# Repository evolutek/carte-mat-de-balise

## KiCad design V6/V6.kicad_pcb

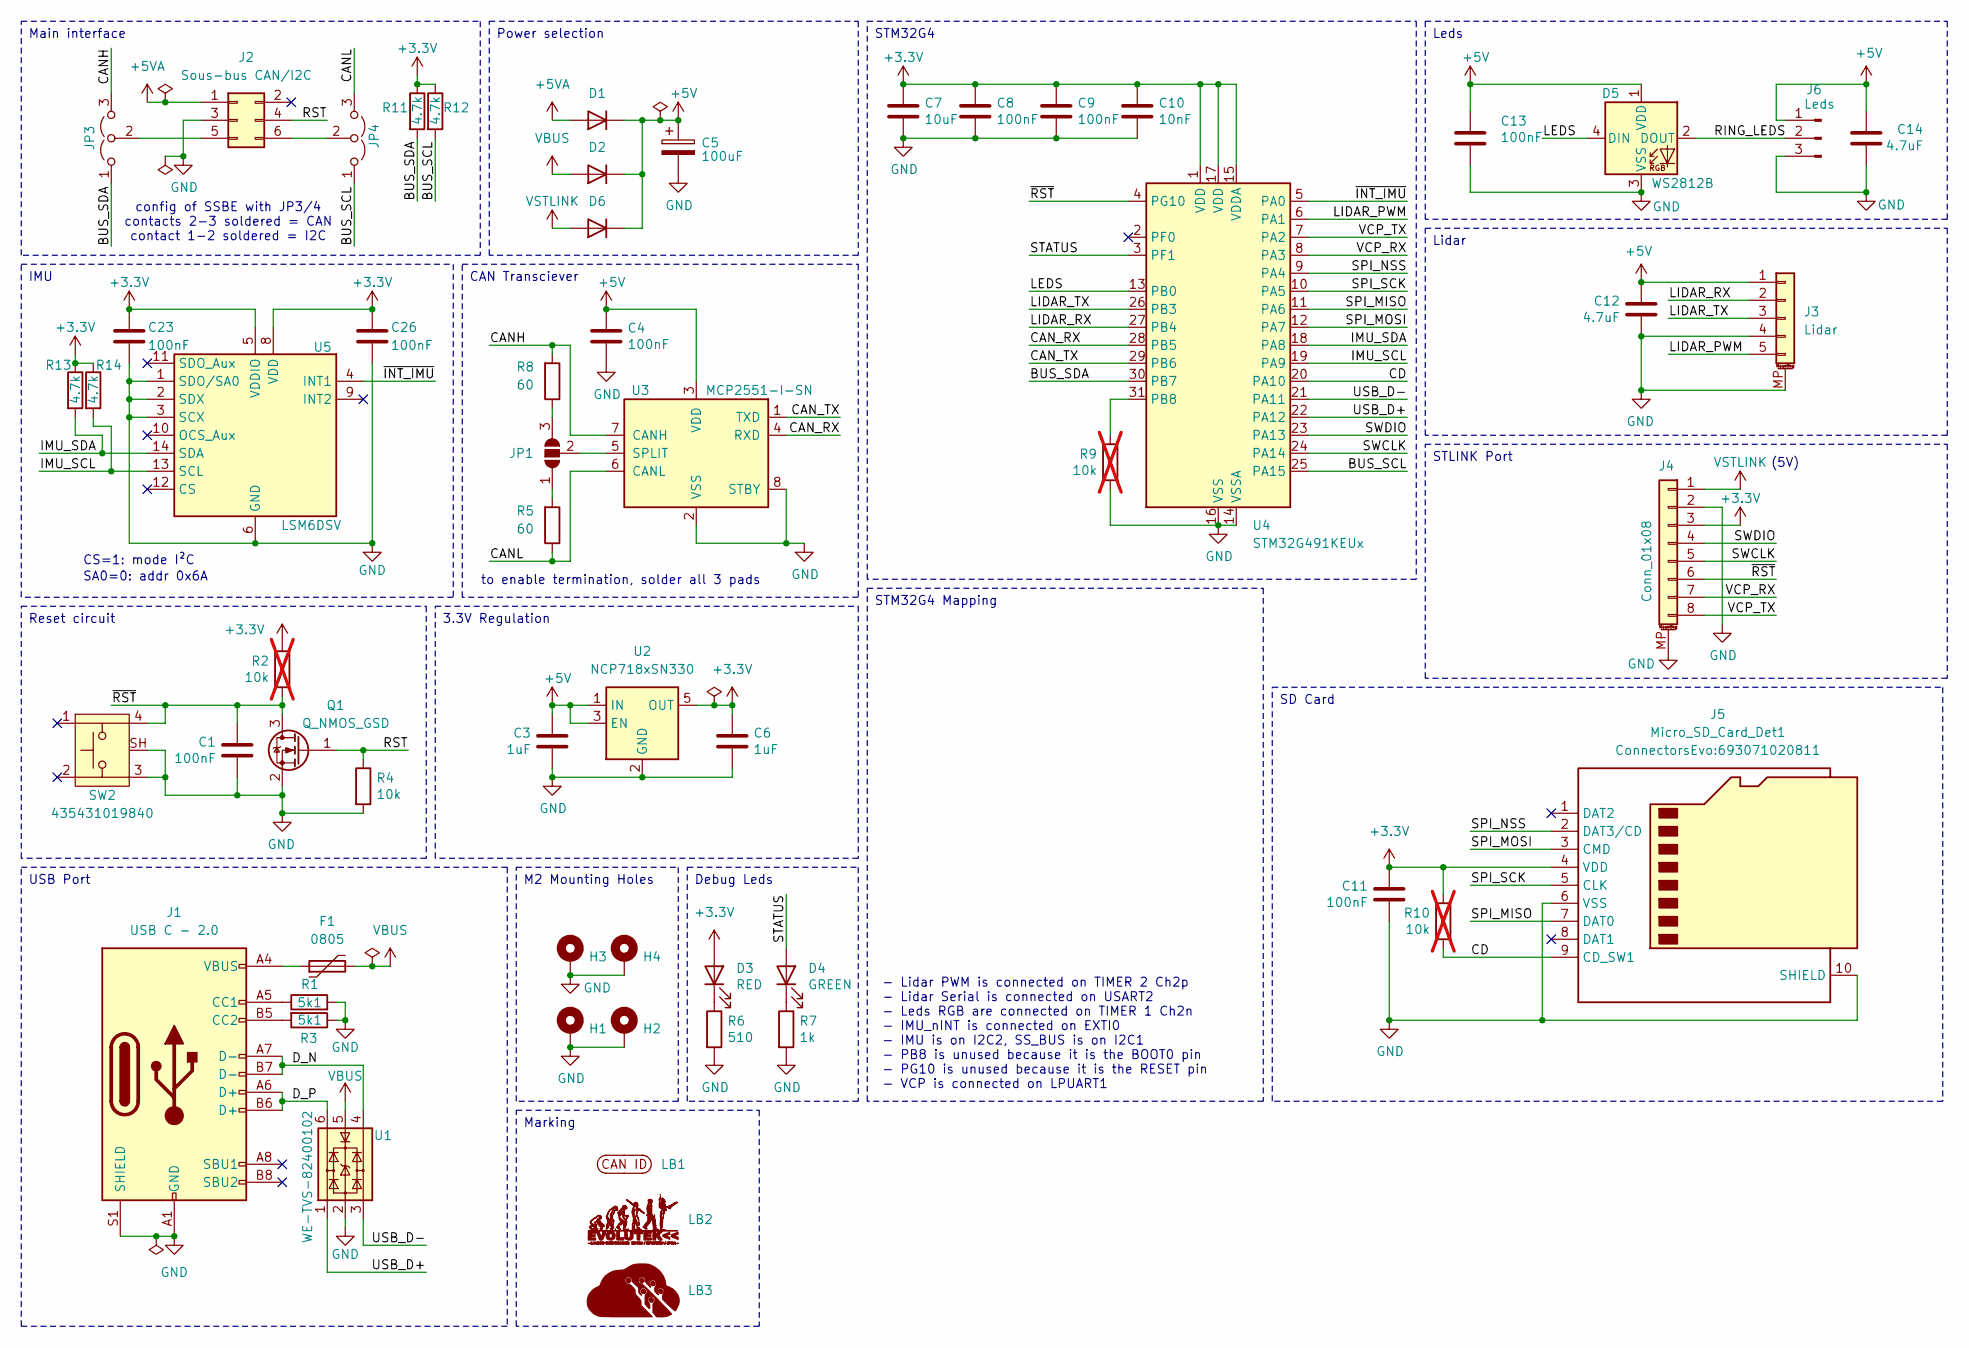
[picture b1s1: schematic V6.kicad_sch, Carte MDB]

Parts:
C1, C4, C8, C9, C11, C13, C23, C26: 100nF; C_0603_1608Metric
C3, C6: 1uF; C_0603_1608Metric
C5: 100uF; C_Elec_6.3x7.7
C7: 10uF; C_0603_1608Metric
C10: 10nF; C_0603_1608Metric
C12, C14: 4.7uF; C_0603_1608Metric
D1, D2, D6: D; D_SOD-523
D3: RED; LED_0805_2012Metric
D4: GREEN; LED_0805_2012Metric
D5: WS2812B; LED_WS2812B_PLCC4_5.0x5.0mm_P3.2mm
F1: 0805; C_0805_2012Metric
H1, H2, H3, H4: MountingHole_Pad; MountingHole_2.2mm_M2_Pad_Via
J1: USB C - 2.0; USB_C_Receptacle_GCT_USB4105-xx-A_16P_TopMnt_Horizontal
J2: Sous-bus CAN/I2C; 690367280676
J3: Lidar; 648105131822
J4: Conn_01x08; 686108188622
J5: Micro_SD_Card_Det1; 693071020811
J6: Leds; S03B-PASK
JP1: Jumper_3_Open; SolderJumper-3_P1.3mm_Open_RoundedPad1.0x1.5mm
JP3, JP4: Jumper_3_Open; SolderJumper-3_P1.3mm_Open_RoundedPad1.0x1.5mm_NumberLabels
LB1: CAN ID lablel
LB2: LOGO; logo-evo-min
LB3: LOGO; Logo Aisler Min
Q1: Q_NMOS_GSD; SOT-23
R1, R3: 5k1; R_0603_1608Metric
R2, R9, R10: 10k; R_0603_1608Metric; not fitted
R4: 10k; R_0603_1608Metric
R5, R8: 60; R_0603_1608Metric
R6: 510; R_0603_1608Metric
R7: 1k; R_0603_1608Metric
R11, R12, R13, R14: 4.7k; R_0603_1608Metric
SW2: 435431019840
U1: WE-TVS-82400102; SOT-23-6
U2: NCP718xSN330; SOT-23-5
U3: MCP2551-I-SN; SOIC-8_3.9x4.9mm_P1.27mm
U4: STM32G491KEUx; QFN-32-1EP_5x5mm_P0.5mm_EP3.45x3.45mm-Without thermal pad
U5: LSM6DSV; LGA-14_3x2.5mm_P0.5mm_LayoutBorder3x4y

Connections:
+3.3V: C6.1, C7.1, C8.1, C9.1, C10.1, C11.1, C23.1, C26.1, D3.2 (A), J4.3, J5.4 (VDD), R2.1, R10.1, R11.1, R12.1, R13.1, R14.1, U2.5 (OUT), U4.1 (VDD), U4.15 (VDDA), U4.17 (VDD), U5.5 (VDDIO), U5.8 (VDD)
+5V: C3.1, C4.1, C5.1, C12.1, C13.1, C14.1, D1.1 (K), D2.1 (K), D5.1 (VDD), D6.1 (K), J3.1, J6.1, U2.1 (IN), U2.3 (EN), U3.3 (VDD)
+5VA: D1.2 (A), J2.1
/BUS_SCL: JP4.1 (A), R12.2, U4.25 (PA15)
/BUS_SDA: JP3.1 (A), R11.2, U4.30 (PB7)
/CANH: JP3.3 (B), R8.2, U3.7 (CANH)
/CANL: JP4.3 (B), R5.1, U3.6 (CANL)
/CAN_RX: U3.4 (RXD), U4.28 (PB5)
/CAN_TX: U3.1 (TXD), U4.29 (PB6)
/CD: J5.9 (CD_SW1), R10.2, U4.20 (PA10)
/D_N: J1.A7 (D-), J1.B7 (D-), U1.4
/D_P: J1.A6 (D+), J1.B6 (D+), U1.6
/IMU_SCL: R14.2, U4.19 (PA9), U5.13 (SCL)
/IMU_SDA: R13.2, U4.18 (PA8), U5.14 (SDA)
/LEDS: D5.4 (DIN), U4.13 (PB0)
/LIDAR_PWM: J3.5, U4.6 (PA1)
/LIDAR_RX: J3.2, U4.27 (PB4)
/LIDAR_TX: J3.3, U4.26 (PB3)
/RING_LEDS: D5.2 (DOUT), J6.2
/RST: J2.4, Q1.1 (G), R4.1
/SPI_MISO: J5.7 (DAT0), U4.11 (PA6)
/SPI_MOSI: J5.3 (CMD), U4.12 (PA7)
/SPI_NSS: J5.2 (DAT3/CD), U4.9 (PA4)
/SPI_SCK: J5.5 (CLK), U4.10 (PA5)
/STATUS: D4.2 (A), U4.3 (PF1)
/SWCLK: J4.5, U4.24 (PA14)
/SWDIO: J4.4, U4.23 (PA13)
/USB_D+: U1.1, U4.22 (PA12)
/USB_D-: U1.3, U4.21 (PA11)
/VCP_RX: J4.7, U4.8 (PA3)
/VCP_TX: J4.8, U4.7 (PA2)
/~INT_IMU: U4.5 (PA0), U5.4 (INT1)
/~RST: C1.1, J4.6, Q1.3 (D), R2.2, SW2.4, U4.4 (PG10)
GND: C1.2, C3.2, C4.2, C5.2, C6.2, C7.2, C8.2, C9.2, C10.2, C11.2, C12.2, C13.2, C14.2, C23.2, C26.2, D5.3 (VSS), H1.1, H2.1, H3.1, H4.1, J1.A1 (GND), J1.A12 (GND), J1.B1 (GND), J1.B12 (GND), J1.S1 (SHIELD), J2.3, J3.4, J3.MP (MountPin), J4.2, J4.MP (MountPin), J5.6 (VSS), J5.10 (SHIELD), J5.11 (SHIELD), J5.12 (SHIELD), J5.13 (SHIELD), J6.3, Q1.2 (S), R1.2, R3.1, R4.2, R6.2, R7.2, R9.2, SW2.3, SW2.SH, U1.2, U2.2 (GND), U3.2 (VSS), U3.8 (STBY), U4.14 (VSSA), U4.16 (VSS), U4.32 (VSS), U5.1 (SDO/SA0), U5.2 (SDX), U5.3 (SCX), U5.6 (GND), U5.7 (GND)
unnamed: D3.1 (K), R6.1
unnamed: D4.1 (K), R7.1
unnamed: F1.1, J1.A4 (VBUS), J1.A9 (VBUS), J1.B4 (VBUS), J1.B9 (VBUS)
unnamed: J1.A5 (CC1), R1.1
unnamed: J1.B5 (CC2), R3.2
unnamed: J2.5, JP3.2 (C)
unnamed: J2.6, JP4.2 (C)
unnamed: JP1.1 (A), R5.2
unnamed: JP1.3 (B), R8.1
unnamed: JP1.2 (C), U3.5 (SPLIT)
unnamed: R9.1, U4.31 (PB8)
VBUS: D2.2 (A), F1.2, U1.5
VSTLINK: D6.2 (A), J4.1

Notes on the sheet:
to enable termination, solder all 3 pads
CS=1: mode I²C
- Lidar PWM is connected on TIMER 2 Ch2p - Lidar Serial is connected on USART2 - Leds RGB are connected on TIMER 1 Ch2n - IMU_nINT is connected on EXTI0 - IMU is on I2C2, SS_BUS is on I2C1 - PB8 is unused because it is the BOOT0 pin - PG10 is unused because it is the RESET pin - VCP is connected on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
SA0=0: addr 0x6A
(5V)
config of SSBE with JP3/4 contacts 2-3 soldered = CAN contact 1-2 soldered = I2C
USB Port
CAN Transciever
Main interface
Power selection
3.3V Regulation
Lidar
Leds
M2 Mounting Holes
STM32G4
Reset circuit
SD Card
Debug Leds
Marking
STLINK Port
IMU
STM32G4 Mapping

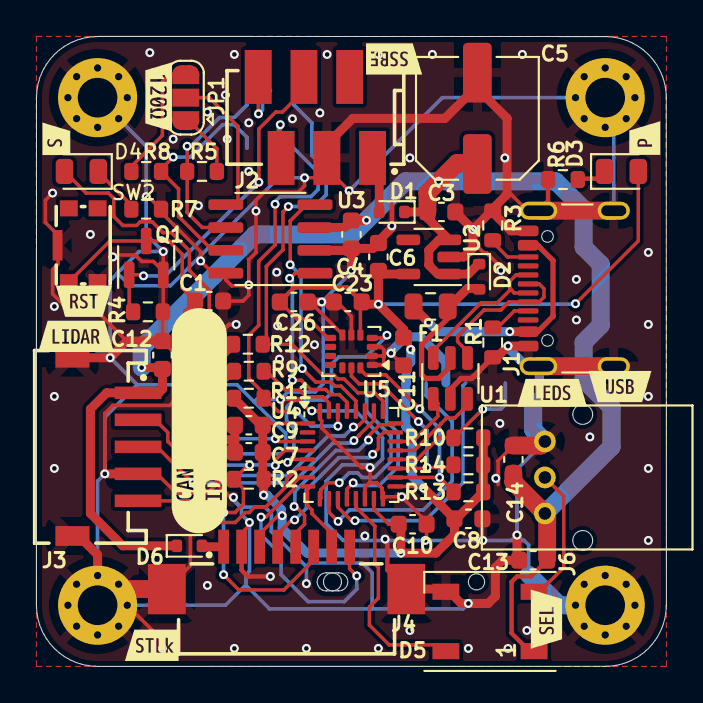
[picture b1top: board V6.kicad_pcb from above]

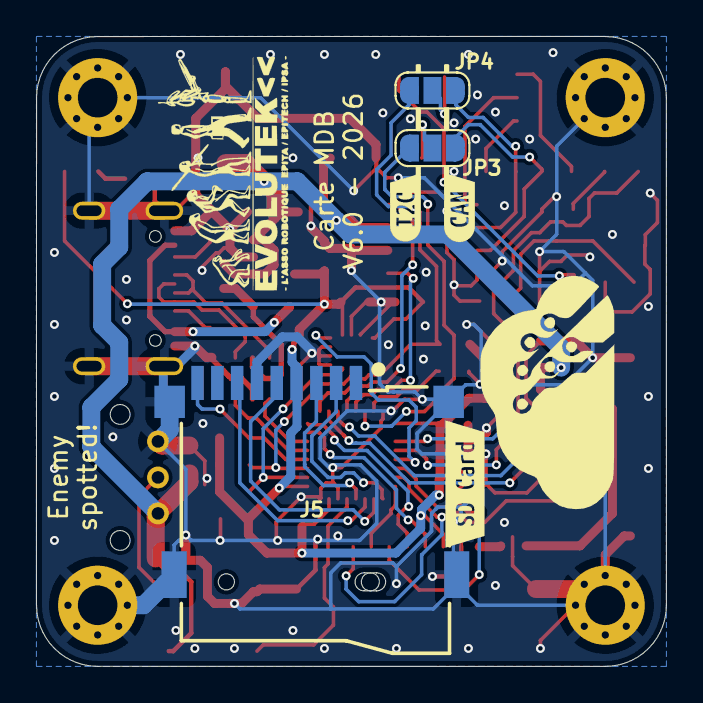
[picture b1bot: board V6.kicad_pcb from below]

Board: 2 copper layers, 35.0 x 35.0 mm, 72 parts (8 on the bottom side), 47 nets.

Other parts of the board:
kibuzzard-69B5B6D5: G***; kibuzzard-69B5B6D5
kibuzzard-69B5B6FD: G***; kibuzzard-69B5B6FD
kibuzzard-69B5B77E: G***; kibuzzard-69B5B77E
kibuzzard-69B5B785: G***; kibuzzard-69B5B785
kibuzzard-69B5BD1F: G***; kibuzzard-69B5BD1F
kibuzzard-69B5BF2C: G***; kibuzzard-69B5BF2C
kibuzzard-69B5BF9D: G***; kibuzzard-69B5BF9D
kibuzzard-69B5C02D: G***; kibuzzard-69B5C02D
kibuzzard-69B5C08C: G***; kibuzzard-69B5C08C
kibuzzard-69B5C131: G***; kibuzzard-69B5C131
kibuzzard-69B5C209: G***; kibuzzard-69B5C209
kibuzzard-69B5C219: G***; kibuzzard-69B5C219
kibuzzard-672938AE: G***; kibuzzard-672938AE

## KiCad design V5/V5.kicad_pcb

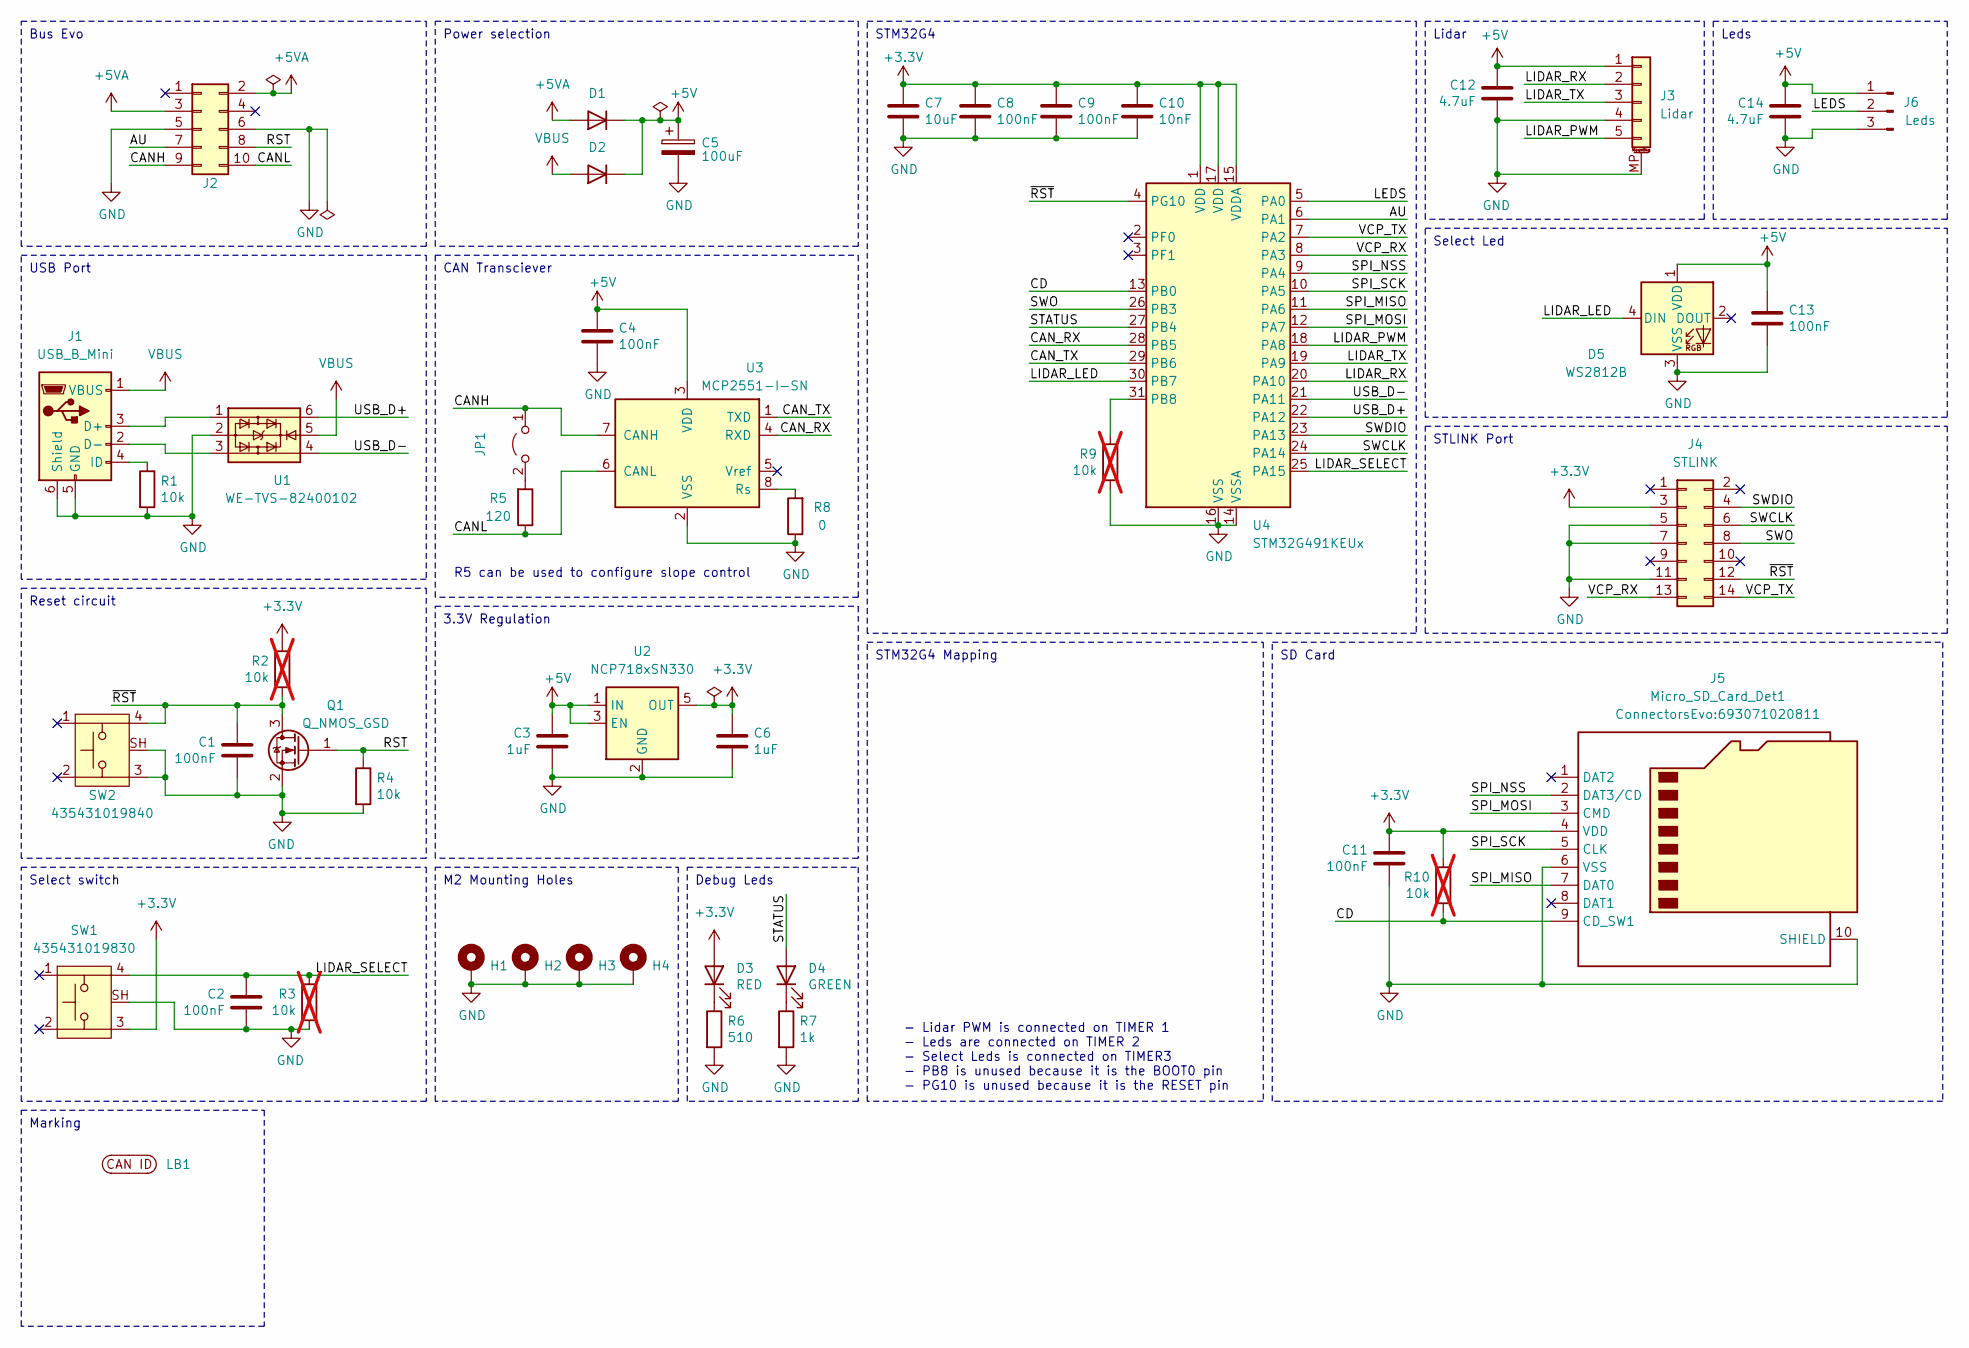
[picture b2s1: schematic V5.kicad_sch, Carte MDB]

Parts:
C1, C2, C4, C8, C9, C11, C13: 100nF; C_0603_1608Metric
C3, C6: 1uF; C_0603_1608Metric
C5: 100uF; C_Elec_6.3x7.7
C7: 10uF; C_0603_1608Metric
C10: 10nF; C_0603_1608Metric
C12, C14: 4.7uF; C_0603_1608Metric
D1, D2: D; D_SOD-523
D3: RED; LED_0805_2012Metric
D4: GREEN; LED_0805_2012Metric
D5: WS2812B; LED_WS2812B_PLCC4_5.0x5.0mm_P3.2mm
H1, H2, H3, H4: MountingHole_Pad; MountingHole_2.2mm_M2_Pad_Via
J1: USB_B_Mini; USB_Mini-B_Wuerth_65100516121_Horizontal
J2: Conn_02x05_Odd_Even; 690367281076
J3: Lidar; 648105131822
J4: STLINK; 62701420621
J5: Micro_SD_Card_Det1; 693071020811
J6: Leds; S03B-PASK
JP1: Jumper_2_Open; PinHeader_1x02_P2.54mm_Vertical
LB1: CAN ID lablel
Q1: Q_NMOS_GSD; SOT-23
R1, R4: 10k; R_0603_1608Metric
R2, R3, R9, R10: 10k; R_0603_1608Metric; not fitted
R5: 120; R_0603_1608Metric
R6: 510; R_0603_1608Metric
R7: 1k; R_0603_1608Metric
R8: 0; R_0603_1608Metric
SW1: 435431019830
SW2: 435431019840
U1: WE-TVS-82400102; SOT-23-6
U2: NCP718xSN330; SOT-23-5
U3: MCP2551-I-SN; SOIC-8_3.9x4.9mm_P1.27mm
U4: STM32G491KEUx; QFN-32-1EP_5x5mm_P0.5mm_EP3.45x3.45mm-Without thermal pad

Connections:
+3.3V: C6.1, C7.1, C8.1, C9.1, C10.1, C11.1, D3.2 (A), J4.3, J5.4 (VDD), R2.1, R10.1, SW1.3, U2.5 (OUT), U4.1 (VDD), U4.15 (VDDA), U4.17 (VDD)
+5V: C3.1, C4.1, C5.1, C12.1, C13.1, C14.1, D1.1 (K), D2.1 (K), D5.1 (VDD), J3.1, J6.1, U2.1 (IN), U2.3 (EN), U3.3 (VDD)
+5VA: D1.2 (A), J2.2, J2.3
/AU: J2.7, U4.6 (PA1)
/CANH: J2.9, JP1.1 (A), U3.7 (CANH)
/CANL: J2.10, R5.1, U3.6 (CANL)
/CAN_RX: U3.4 (RXD), U4.28 (PB5)
/CAN_TX: U3.1 (TXD), U4.29 (PB6)
/CD: J5.9 (CD_SW1), R10.2, U4.13 (PB0)
/LEDS: J6.2, U4.5 (PA0)
/LIDAR_LED: D5.4 (DIN), U4.30 (PB7)
/LIDAR_PWM: J3.5, U4.18 (PA8)
/LIDAR_RX: J3.2, U4.20 (PA10)
/LIDAR_SELECT: C2.1, R3.1, SW1.4, U4.25 (PA15)
/LIDAR_TX: J3.3, U4.19 (PA9)
/RST: J2.8, Q1.1 (G), R4.1
/SPI_MISO: J5.7 (DAT0), U4.11 (PA6)
/SPI_MOSI: J5.3 (CMD), U4.12 (PA7)
/SPI_NSS: J5.2 (DAT3/CD), U4.9 (PA4)
/SPI_SCK: J5.5 (CLK), U4.10 (PA5)
/STATUS: D4.2 (A), U4.27 (PB4)
/SWCLK: J4.6, U4.24 (PA14)
/SWDIO: J4.4, U4.23 (PA13)
/SWO: J4.8, U4.26 (PB3)
/USB_D+: U1.6, U4.22 (PA12)
/USB_D-: U1.4, U4.21 (PA11)
/VCP_RX: J4.13, U4.8 (PA3)
/VCP_TX: J4.14, U4.7 (PA2)
/~RST: C1.1, J4.12, Q1.3 (D), R2.2, SW2.4, U4.4 (PG10)
GND: C1.2, C2.2, C3.2, C4.2, C5.2, C6.2, C7.2, C8.2, C9.2, C10.2, C11.2, C12.2, C13.2, C14.2, D5.3 (VSS), H1.1, H2.1, H3.1, H4.1, J1.5 (GND), J1.6 (Shield), J2.5, J2.6, J3.4, J3.MP (MountPin), J4.5, J4.7, J4.11, J5.6 (VSS), J5.10 (SHIELD), J5.11 (SHIELD), J5.12 (SHIELD), J5.13 (SHIELD), J6.3, Q1.2 (S), R1.2, R3.2, R4.2, R6.2, R7.2, R8.1, R9.2, SW1.SH, SW2.3, SW2.SH, U1.2, U2.2 (GND), U3.2 (VSS), U4.14 (VSSA), U4.16 (VSS), U4.32 (VSS)
unnamed: D3.1 (K), R6.1
unnamed: D4.1 (K), R7.1
unnamed: J1.3 (D+), U1.1
unnamed: J1.2 (D-), U1.3
unnamed: J1.4 (ID), R1.1
unnamed: JP1.2 (B), R5.2
unnamed: R8.2, U3.8 (Rs)
unnamed: R9.1, U4.31 (PB8)
VBUS: D2.2 (A), J1.1 (VBUS), U1.5

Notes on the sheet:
Select Led
USB Port
CAN Transciever
Power selection
3.3V Regulation
Lidar
Leds
M2 Mounting Holes
STM32G4
Reset circuit
Select switch
SD Card
Debug Leds
Marking
Bus Evo
STLINK Port
STM32G4 Mapping
R5 can be used to configure slope control
- Lidar PWM is connected on TIMER 1 - Leds are connected on TIMER 2 - Select Leds is connected on TIMER3 - PB8 is unused because it is the BOOT0 pin - PG10 is unused because it is the RESET pin

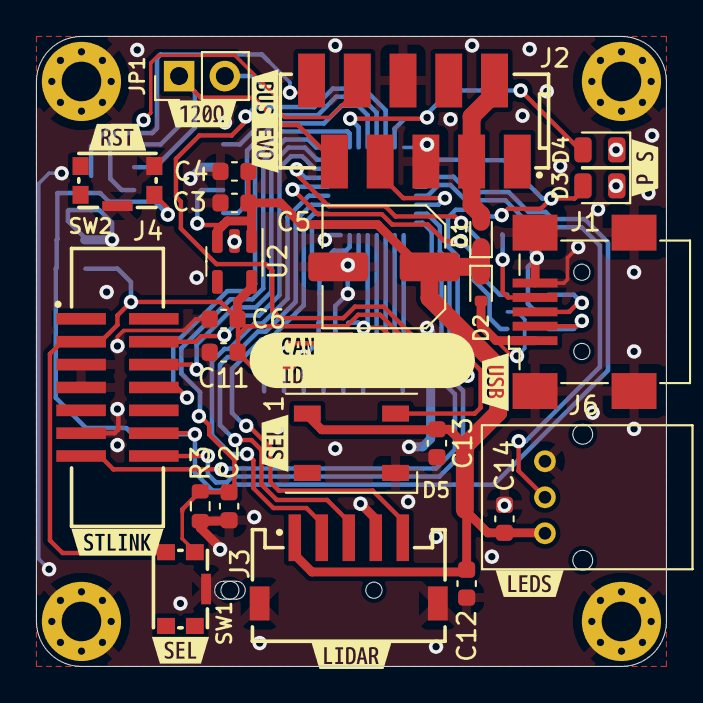
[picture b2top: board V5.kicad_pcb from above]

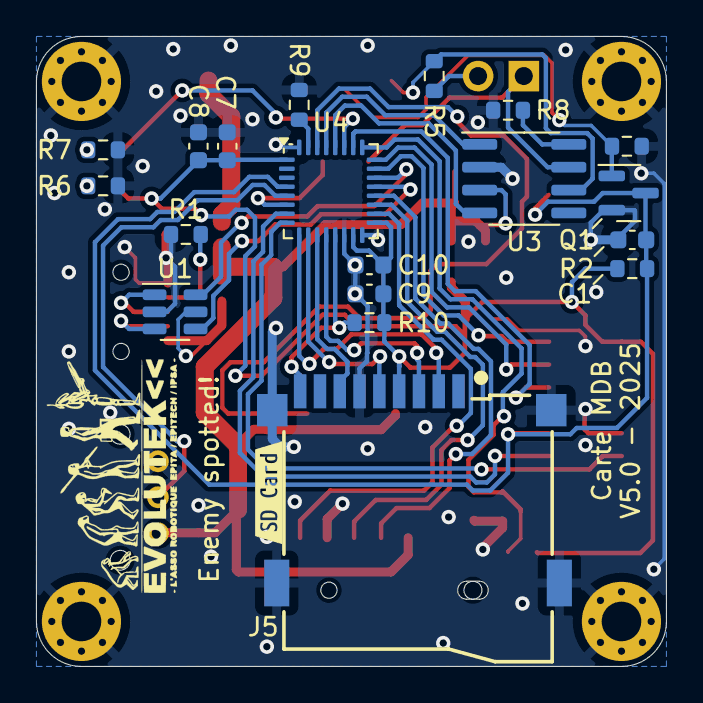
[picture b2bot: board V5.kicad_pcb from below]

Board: 2 copper layers, 35.0 x 35.0 mm, 59 parts (20 on the bottom side), 39 nets.

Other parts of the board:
kibuzzard-672938AE: G***; kibuzzard-672938AE
kibuzzard-672938F5: G***; kibuzzard-672938F5
kibuzzard-672939DE: G***; kibuzzard-672939DE
kibuzzard-672956A1: G***; kibuzzard-672956A1
kibuzzard-6729394F: G***; kibuzzard-6729394F
kibuzzard-67293773: G***; kibuzzard-67293773
kibuzzard-67293797: G***; kibuzzard-67293797
kibuzzard-67293826: G***; kibuzzard-67293826
kibuzzard-67293839: G***; kibuzzard-67293839
kibuzzard-67293907: G***; kibuzzard-67293907
kibuzzard-67293975: G***; kibuzzard-67293975

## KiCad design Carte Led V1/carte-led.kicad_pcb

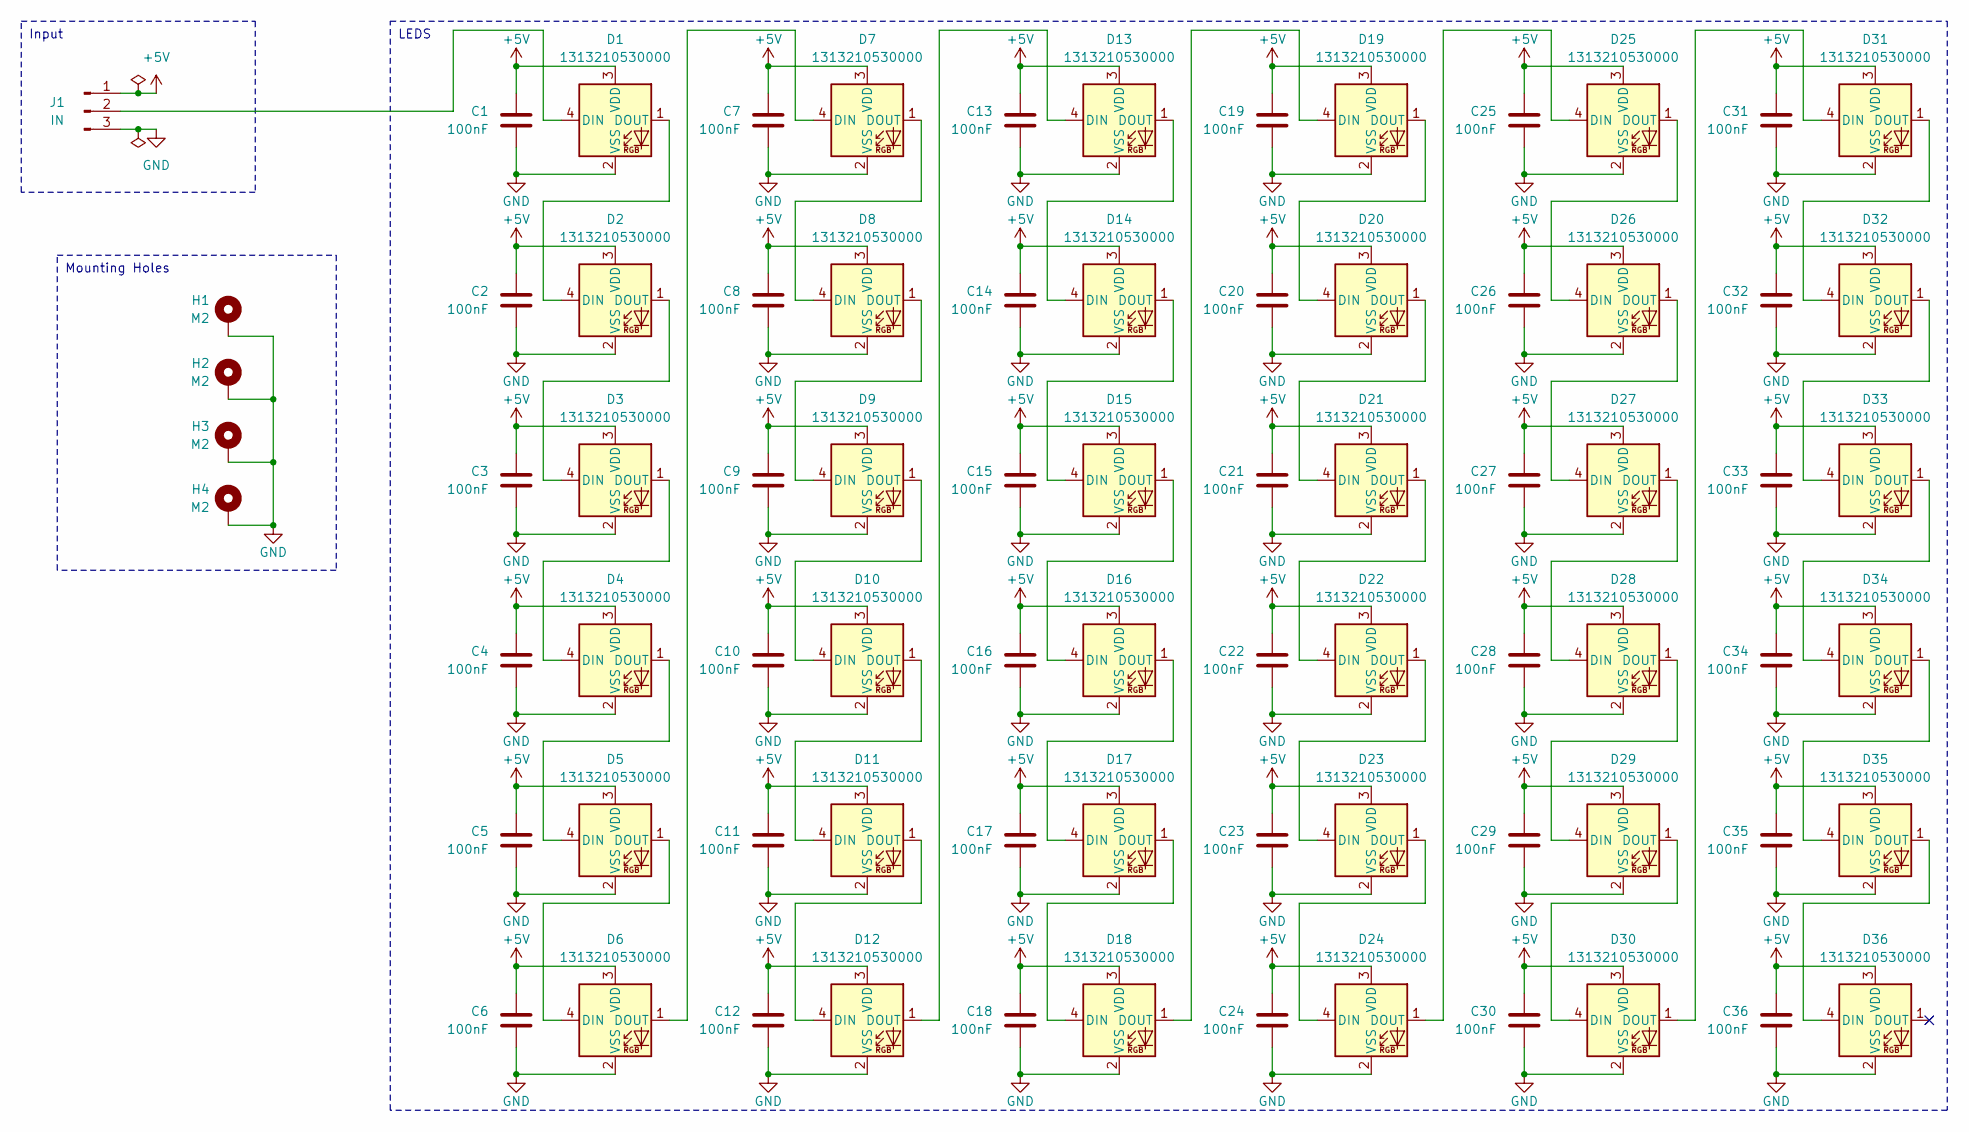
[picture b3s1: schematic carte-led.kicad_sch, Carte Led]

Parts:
C1, C2, C3, C4, C5, C6, C7, C8, C9, C10, C11, C12, C13, C14, C15, C16, C17, C18, C19, C20, C21, C22, C23, C24, C25, C26, C27, C28, C29, C30, C31, C32, C33, C34, C35, C36: 100nF; C_0603_1608Metric
D1, D2, D3, D4, D5, D6, D7, D8, D9, D10, D11, D12, D13, D14, D15, D16, D17, D18, D19, D20, D21, D22, D23, D24, D25, D26, D27, D28, D29, D30, D31, D32, D33, D34, D35, D36: 1313210530000
H1, H2, H3, H4: M2; MountingHole_2.2mm_M2_Pad_Via
J1: IN; B03B-PASK

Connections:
+5V: C1.1, C2.1, C3.1, C4.1, C5.1, C6.1, C7.1, C8.1, C9.1, C10.1, C11.1, C12.1, C13.1, C14.1, C15.1, C16.1, C17.1, C18.1, C19.1, C20.1, C21.1, C22.1, C23.1, C24.1, C25.1, C26.1, C27.1, C28.1, C29.1, C30.1, C31.1, C32.1, C33.1, C34.1, C35.1, C36.1, D1.3 (VDD), D2.3 (VDD), D3.3 (VDD), D4.3 (VDD), D5.3 (VDD), D6.3 (VDD), D7.3 (VDD), D8.3 (VDD), D9.3 (VDD), D10.3 (VDD), D11.3 (VDD), D12.3 (VDD), D13.3 (VDD), D14.3 (VDD), D15.3 (VDD), D16.3 (VDD), D17.3 (VDD), D18.3 (VDD), D19.3 (VDD), D20.3 (VDD), D21.3 (VDD), D22.3 (VDD), D23.3 (VDD), D24.3 (VDD), D25.3 (VDD), D26.3 (VDD), D27.3 (VDD), D28.3 (VDD), D29.3 (VDD), D30.3 (VDD), D31.3 (VDD), D32.3 (VDD), D33.3 (VDD), D34.3 (VDD), D35.3 (VDD), D36.3 (VDD), J1.1
GND: C1.2, C2.2, C3.2, C4.2, C5.2, C6.2, C7.2, C8.2, C9.2, C10.2, C11.2, C12.2, C13.2, C14.2, C15.2, C16.2, C17.2, C18.2, C19.2, C20.2, C21.2, C22.2, C23.2, C24.2, C25.2, C26.2, C27.2, C28.2, C29.2, C30.2, C31.2, C32.2, C33.2, C34.2, C35.2, C36.2, D1.2 (VSS), D2.2 (VSS), D3.2 (VSS), D4.2 (VSS), D5.2 (VSS), D6.2 (VSS), D7.2 (VSS), D8.2 (VSS), D9.2 (VSS), D10.2 (VSS), D11.2 (VSS), D12.2 (VSS), D13.2 (VSS), D14.2 (VSS), D15.2 (VSS), D16.2 (VSS), D17.2 (VSS), D18.2 (VSS), D19.2 (VSS), D20.2 (VSS), D21.2 (VSS), D22.2 (VSS), D23.2 (VSS), D24.2 (VSS), D25.2 (VSS), D26.2 (VSS), D27.2 (VSS), D28.2 (VSS), D29.2 (VSS), D30.2 (VSS), D31.2 (VSS), D32.2 (VSS), D33.2 (VSS), D34.2 (VSS), D35.2 (VSS), D36.2 (VSS), H1.1, H2.1, H3.1, H4.1, J1.3
unnamed: D1.4 (DIN), J1.2
unnamed: D1.1 (DOUT), D2.4 (DIN)
unnamed: D2.1 (DOUT), D3.4 (DIN)
unnamed: D3.1 (DOUT), D4.4 (DIN)
unnamed: D4.1 (DOUT), D5.4 (DIN)
unnamed: D5.1 (DOUT), D6.4 (DIN)
unnamed: D6.1 (DOUT), D7.4 (DIN)
unnamed: D7.1 (DOUT), D8.4 (DIN)
unnamed: D8.1 (DOUT), D9.4 (DIN)
unnamed: D9.1 (DOUT), D10.4 (DIN)
unnamed: D10.1 (DOUT), D11.4 (DIN)
unnamed: D11.1 (DOUT), D12.4 (DIN)
unnamed: D12.1 (DOUT), D13.4 (DIN)
unnamed: D13.1 (DOUT), D14.4 (DIN)
unnamed: D14.1 (DOUT), D15.4 (DIN)
unnamed: D15.1 (DOUT), D16.4 (DIN)
unnamed: D16.1 (DOUT), D17.4 (DIN)
unnamed: D17.1 (DOUT), D18.4 (DIN)
unnamed: D18.1 (DOUT), D19.4 (DIN)
unnamed: D19.1 (DOUT), D20.4 (DIN)
unnamed: D20.1 (DOUT), D21.4 (DIN)
unnamed: D21.1 (DOUT), D22.4 (DIN)
unnamed: D22.1 (DOUT), D23.4 (DIN)
unnamed: D23.1 (DOUT), D24.4 (DIN)
unnamed: D24.1 (DOUT), D25.4 (DIN)
unnamed: D25.1 (DOUT), D26.4 (DIN)
unnamed: D26.1 (DOUT), D27.4 (DIN)
unnamed: D27.1 (DOUT), D28.4 (DIN)
unnamed: D28.1 (DOUT), D29.4 (DIN)
unnamed: D29.1 (DOUT), D30.4 (DIN)
unnamed: D30.1 (DOUT), D31.4 (DIN)
unnamed: D31.1 (DOUT), D32.4 (DIN)
unnamed: D32.1 (DOUT), D33.4 (DIN)
unnamed: D33.1 (DOUT), D34.4 (DIN)
unnamed: D34.1 (DOUT), D35.4 (DIN)
unnamed: D35.1 (DOUT), D36.4 (DIN)

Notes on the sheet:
Mounting Holes
LEDS
Input

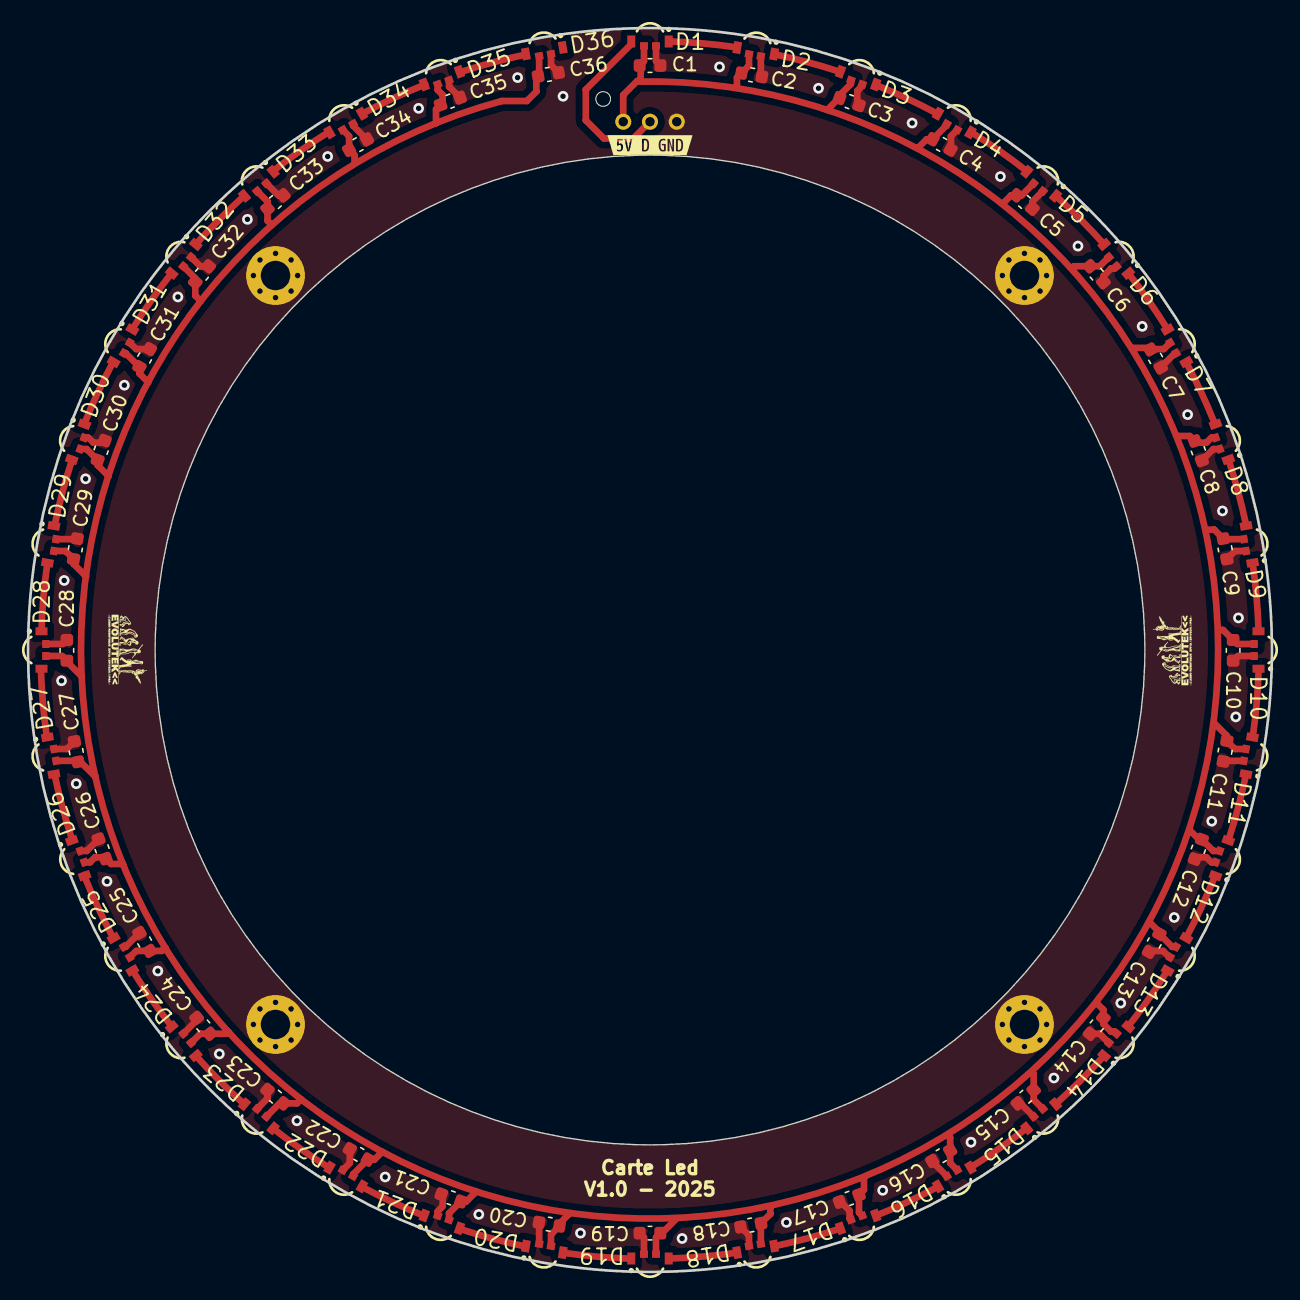
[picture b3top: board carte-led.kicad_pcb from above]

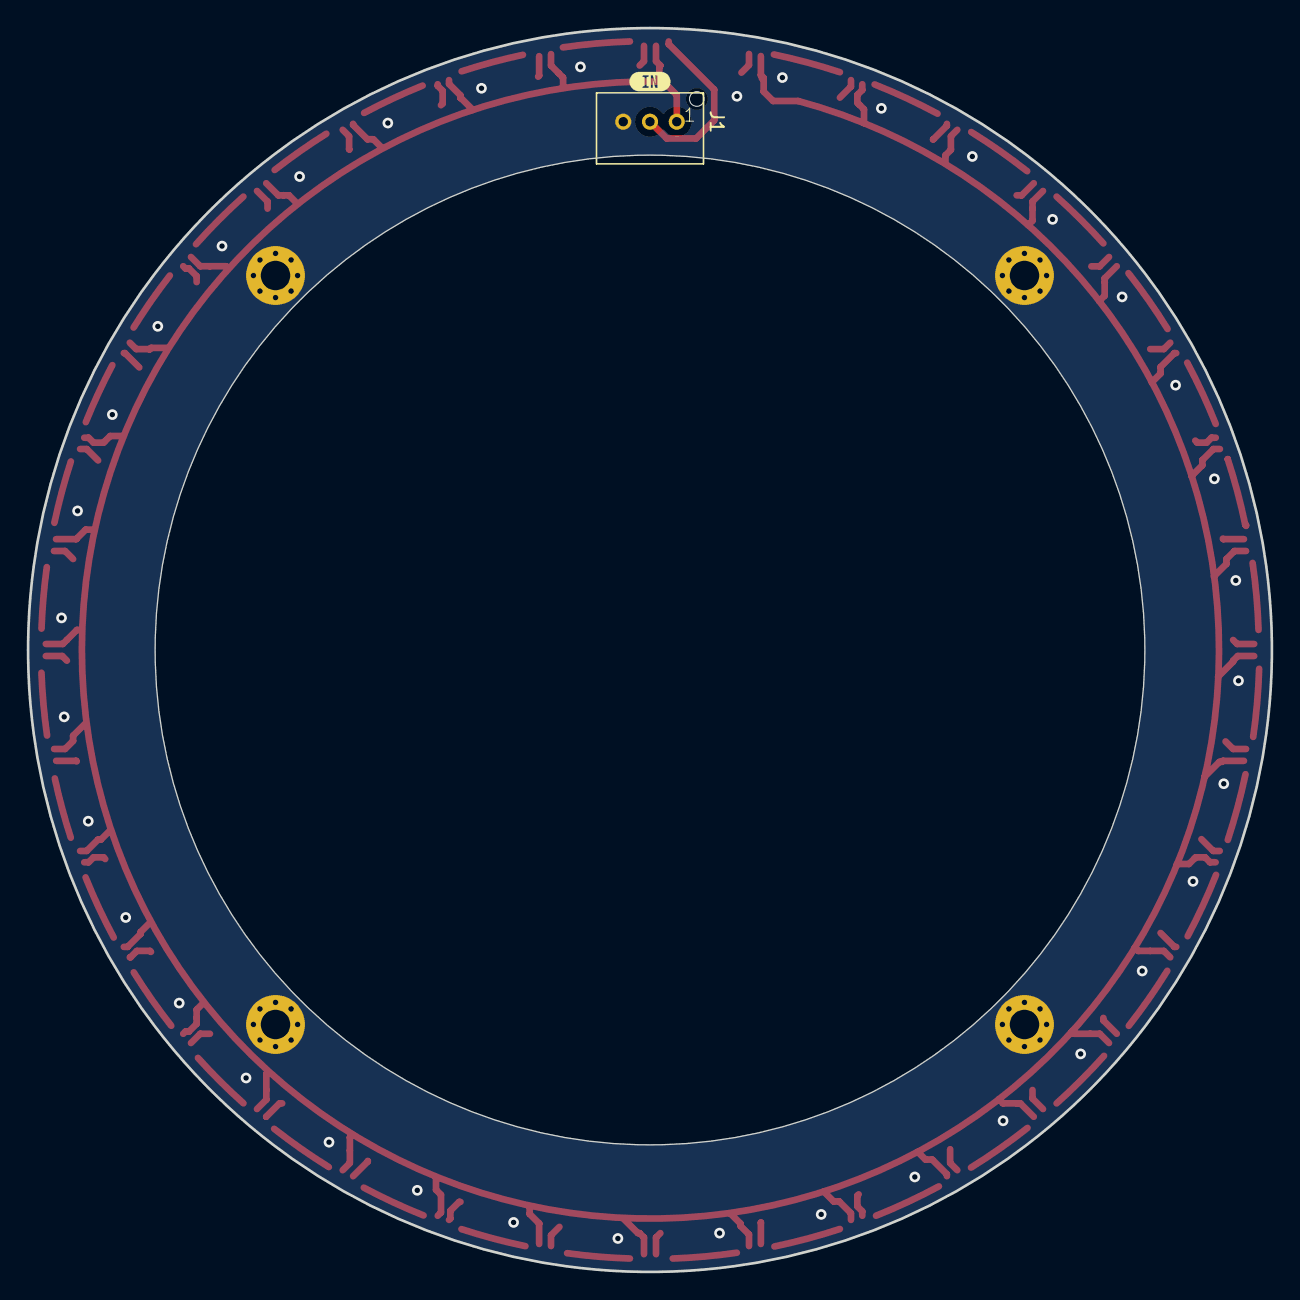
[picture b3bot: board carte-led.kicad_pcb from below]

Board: 2 copper layers, 93.0 x 93.0 mm, 79 parts (2 on the bottom side), 38 nets.

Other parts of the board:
kibuzzard-671BE0FE: G***; kibuzzard-671BE0FE
kibuzzard-671BE04B: G***; kibuzzard-671BE04B

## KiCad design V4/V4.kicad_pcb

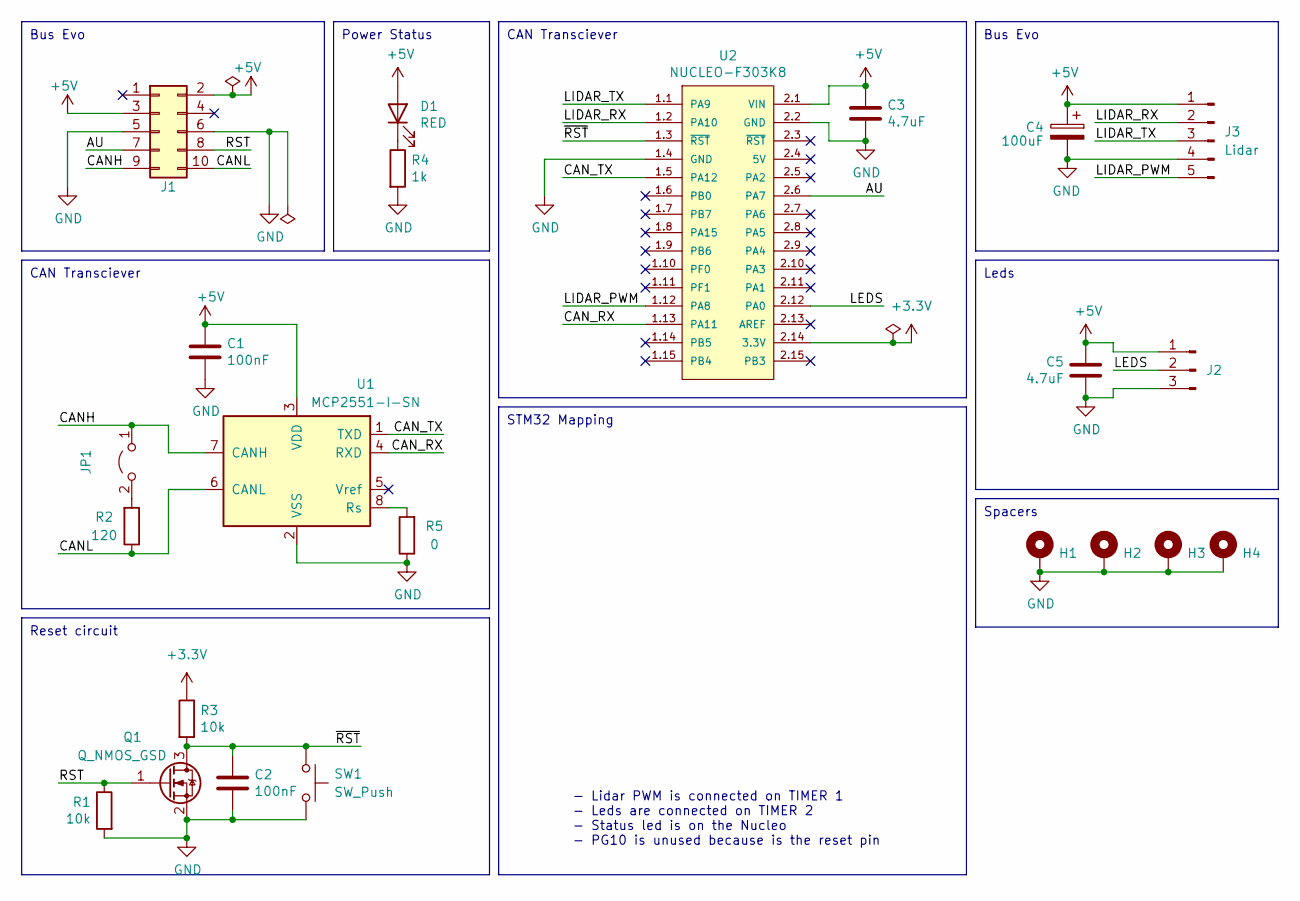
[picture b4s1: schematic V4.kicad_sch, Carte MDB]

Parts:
C1, C2: 100nF; C_0603_1608Metric
C3, C5: 4.7uF; C_0603_1608Metric
C4: 100uF; C_Elec_6.3x7.7
D1: RED; LED_0805_2012Metric
H1, H2, H3, H4: MountingHole_Pad; WA-SMSI_9774030360
J1: Conn_02x05_Odd_Even; 690367281076
J2: Conn_01x03_Male; B03B-PASK
J3: Lidar; JST_XH_B5B-XH-AM_1x05_P2.50mm_Vertical
JP1: Jumper_2_Open; PinHeader_1x02_P2.54mm_Vertical
Q1: Q_NMOS_GSD; SOT-23
R1, R3: 10k; R_0603_1608Metric
R2: 120; R_0603_1608Metric
R4: 1k; R_0603_1608Metric
R5: 0; R_0603_1608Metric
SW1: SW_Push; SW_Tactile_SPST_Angled_PTS645Vx83-2LFS
U1: MCP2551-I-SN; SOIC-8_3.9x4.9mm_P1.27mm
U2: NUCLEO-F303K8; MODULE_NUCLEO-32

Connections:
+3.3V: R3.1, U2.2.14 (3.3V)
+5V: C1.1, C3.1, C4.1, C5.1, D1.2 (A), J1.2, J1.3, J2.1, J3.1, U1.3 (VDD), U2.2.1 (VIN)
/AU: J1.7, U2.2.6 (PA7)
/CANH: J1.9, JP1.1 (A), U1.7 (CANH)
/CANL: J1.10, R2.1, U1.6 (CANL)
/CAN_RX: U1.4 (RXD), U2.1.13 (PA11)
/CAN_TX: U1.1 (TXD), U2.1.5 (PA12)
/LEDS: J2.2, U2.2.12 (PA0)
/LIDAR_PWM: J3.5, U2.1.12 (PA8)
/LIDAR_RX: J3.2, U2.1.2 (PA10)
/LIDAR_TX: J3.3, U2.1.1 (PA9)
/RST: J1.8, Q1.1 (G), R1.1
/~RST: C2.1, Q1.3 (D), R3.2, SW1.1, U2.1.3 (~RST)
GND: C1.2, C2.2, C3.2, C4.2, C5.2, H1.1, H2.1, H3.1, H4.1, J1.5, J1.6, J2.3, J3.4, Q1.2 (S), R1.2, R4.2, R5.1, SW1.2, U1.2 (VSS), U2.1.4 (GND), U2.2.2 (GND)
unnamed: D1.1 (K), R4.1
unnamed: JP1.2 (B), R2.2
unnamed: R5.2, U1.8 (Rs)

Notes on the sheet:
CAN Transciever
Power Status
Bus Evo
Leds
Spacers
Reset circuit
STM32 Mapping
- Lidar PWM is connected on TIMER 1 - Leds are connected on TIMER 2 - Status led is on the Nucleo - PG10 is unused because is the reset pin
